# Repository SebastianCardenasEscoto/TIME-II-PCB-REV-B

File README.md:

# TIME-II-PCB-REV-C
Radical Redesign of PCB for TIME II project of Space Technologies at Cal

## Features
- :computer: STM32 Microcontroller
- :hotsprings: Three FFC Plugs for Plate Heating System (Thermistors and Heaters)
- :gear: Two DRV8837 H-Bridge Motor Controllers
- :electric_plug: OR Gate PMIC for switching between USB and Battery Power
- :floppy_disk: SD Card for Data Logging

## Differences between Previous Revision

1. We received notice that we _may_ be able to use batteries outside of Blue Origin's approved battery list. 

Thus we decided to use lithium batteries which allowed the following simplifications:

- &nbsp;&nbsp;&nbsp;&nbsp; No longer support charging on flight
- Replaced buck converter with LDO as voltage drop is now 3.7V -> 3.3V instead of 5V -> 3.3V

2. The following simplifications were allowed due to mechanical design:
- Only support Brushed DC motors instead of supporting both DC motors and 3 pin servos
- Heater ports have been reduced from 5 to 3

3. The ESP32 microcontoller was replaced with an STM32, mostly to reduce board space since the WiFi and Bluetooth antennae that the ESP offers were unnecessary.

## Pictures

### Schematic

### Layout

## To-Do
- SD card footprint - Week of 3/10/24 [DONE]
- MOSI is connected to DAT0, MISO is connected to CMD. It should be: MOSI is connected to CMD, MISO is connected to DAT0.
- Sanity checks for wiring - week of 3/10/24
- Send board for manufacture - week of 3/10/24

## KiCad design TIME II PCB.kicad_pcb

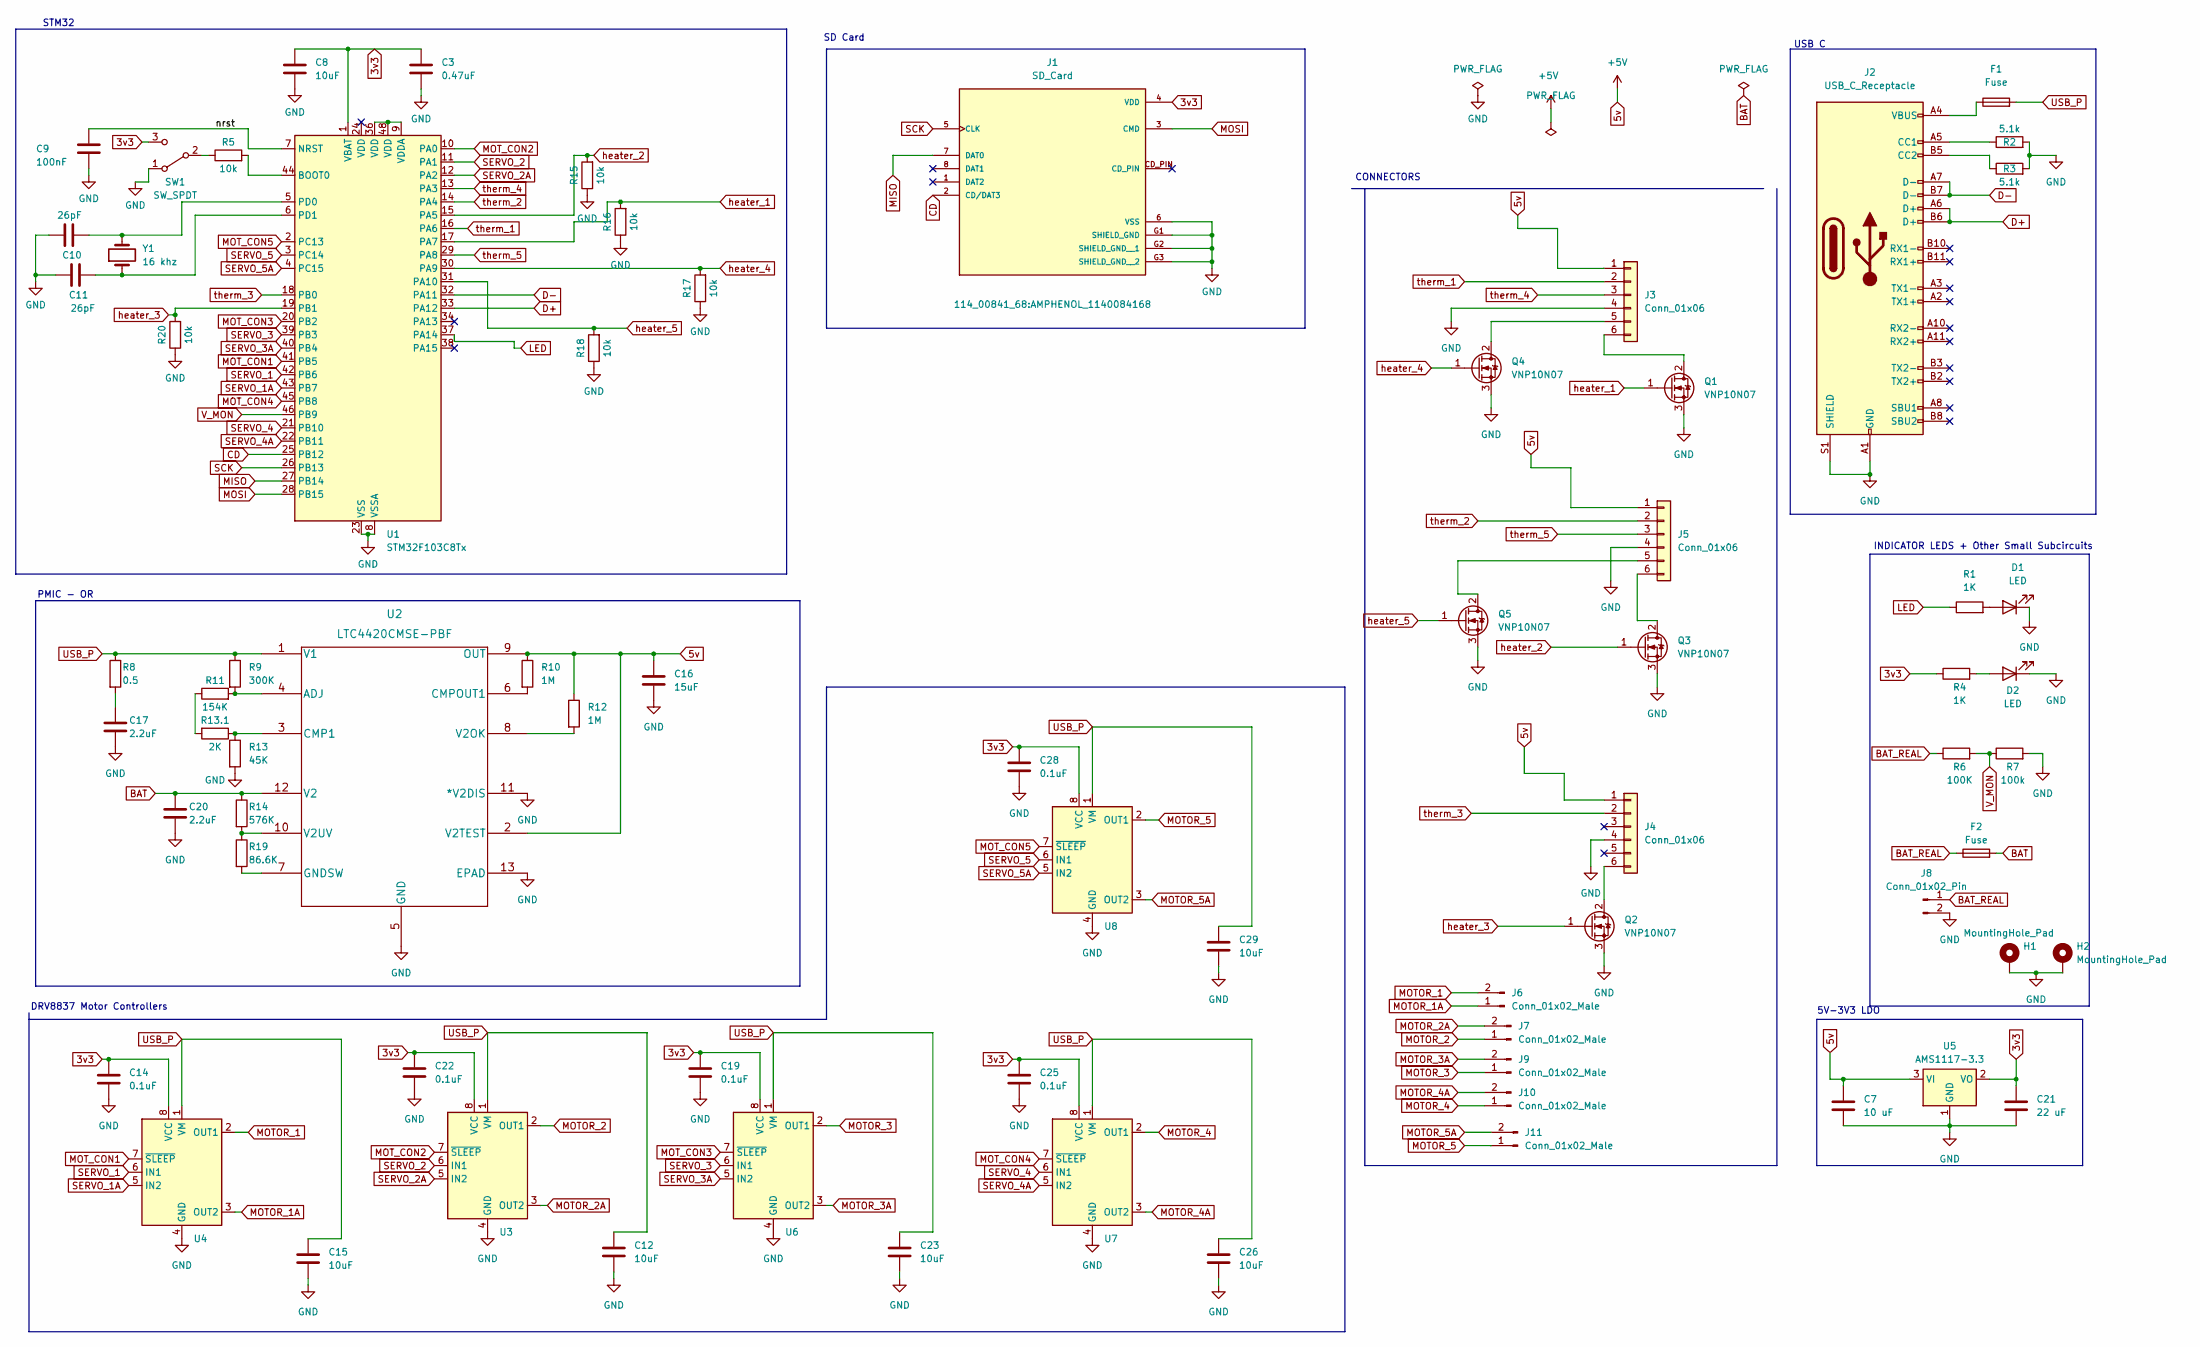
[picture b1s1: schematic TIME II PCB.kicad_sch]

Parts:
C3: 0.47uF; C_0402_1005Metric
C7: 10 uF; C_0402_1005Metric
C8, C12, C15, C23, C26, C29: 10uF; C_0402_1005Metric
C9: 100nF; C_0402_1005Metric
C10, C11: 26pF; C_0402_1005Metric
C14, C19, C22, C25, C28: 0.1uF; C_0402_1005Metric
C16: 15uF; C_0402_1005Metric
C17, C20: 2.2uF; C_0402_1005Metric
C21: 22 uF; C_0402_1005Metric
D1, D2: LED; LED_0603_1608Metric
F1, F2: Fuse; Fuse_0603_1608Metric
H1, H2: MountingHole_Pad; MountingHole_2.5mm_Pad
J1: SD_Card; AMPHENOL_1140084168; PARTREV F
J2: USB_C_Receptacle; USB4105-GF-A
J3, J4, J5: Conn_01x06; CON_525590652_MOL
J6, J7, J9, J10, J11: Conn_01x02_Male; JST_XH_B2B-XH-A_1x02_P2.50mm_Vertical
J8: Conn_01x02_Pin; JST_XH_B2B-XH-AM_1x02_P2.50mm_Vertical
Q1, Q2, Q3, Q4, Q5: VNP10N07; SOT-23-3
R1, R4: 1K; R_0402_1005Metric
R2, R3: 5.1k; R_0402_1005Metric
R5, R15, R16, R17, R18, R20: 10k; R_0402_1005Metric
R6: 100K; R_0402_1005Metric
R7: 100k; R_0402_1005Metric
R8: 0.5; R_0402_1005Metric
R9: 300K; R_0603_1608Metric
R10, R12: 1M; R_0402_1005Metric
R11: 2K; R_0603_1608Metric
R13: 45K; R_0603_1608Metric
R13.1: 154K; R_0603_1608Metric
R14: 576K; R_0402_1005Metric
R19: 86.6K; R_0402_1005Metric
SW1: SW_SPDT; PinHeader_1x03_P1.27mm_Vertical
U1: STM32F103C8Tx; LQFP-48_7x7mm_P0.5mm
U2: LTC4420CMSE-PBF; MSOP-12-1EP_3x4mm_P0.65mm_EP1.65x2.85mm
U3, U4, U6, U7, U8: WSON-8-1EP_2x2mm_P0.5mm_EP0.9x1.6mm_ThermalVias
U5: AMS1117-3.3; SOT-223-3_TabPin2
Y1: 16 khz; abm3

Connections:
3v3: C3.1, C8.1, C14.1, C19.1, C21.1, C22.1, C25.1, C28.1, J1.4 (VDD), R4.1, SW1.3 (C), U1.1 (VBAT), U3.8 (VCC), U4.8 (VCC), U5.2 (VO), U6.8 (VCC), U7.8 (VCC), U8.8 (VCC)
5v: C7.1, C16.1, J3.1, J4.1, J5.1, R10.1, R12.1, U2.2 (V2TEST), U2.9 (OUT), U5.3 (VI)
/nrst: C9.1, U1.7 (NRST)
BAT: C20.1, F2.2, R14.1, U2.12 (V2)
BAT_REAL: F2.1, J8.1, R6.1
CD: J1.2 (CD/DAT3), U1.25 (PB12)
D+: J2.A6 (D+), J2.B6 (D+), U1.33 (PA12)
D-: J2.A7 (D-), J2.B7 (D-), U1.32 (PA11)
GND: C3.2, C7.2, C8.2, C9.2, C10.1, C11.1, C12.2, C14.2, C15.2, C16.2, C17.2, C19.2, C20.2, C21.2, C22.2, C23.2, C25.2, C26.2, C28.2, C29.2, D1.1 (K), D2.1 (K), H1.1, H2.1, J1.6 (VSS), J1.G1 (SHIELD_GND), J1.G2 (SHIELD_GND__1), J1.G3 (SHIELD_GND__2), J2.A1 (GND), J2.A12 (GND), J2.B1 (GND), J2.B12 (GND), J2.S1 (SHIELD), J3.4, J4.4, J5.4, J8.2, Q1.3 (S), Q2.3 (S), Q3.3 (S), Q4.3 (S), Q5.3 (S), R2.2, R3.2, R7.2, R13.2, R15.1, R16.1, R17.1, R18.1, R20.1, SW1.1 (A), U1.8 (VSSA), U1.23 (VSS), U1.35 (VSS), U1.47 (VSS), U2.5 (GND), U2.11 (*V2DIS), U2.13 (EPAD), U3.4 (GND), U3.9 (GND), U4.4 (GND), U4.9 (GND), U5.1 (GND), U6.4 (GND), U6.9 (GND), U7.4 (GND), U7.9 (GND), U8.4 (GND), U8.9 (GND)
LED: R1.1, U1.37 (PA14)
MISO: J1.7 (DAT0), U1.27 (PB14)
MOSI: J1.3 (CMD), U1.28 (PB15)
MOTOR_1: J6.2, U4.2 (OUT1)
MOTOR_1A: J6.1, U4.3 (OUT2)
MOTOR_2: J7.1, U3.2 (OUT1)
MOTOR_2A: J7.2, U3.3 (OUT2)
MOTOR_3: J9.1, U6.2 (OUT1)
MOTOR_3A: J9.2, U6.3 (OUT2)
MOTOR_4: J10.1, U7.2 (OUT1)
MOTOR_4A: J10.2, U7.3 (OUT2)
MOTOR_5: J11.1, U8.2 (OUT1)
MOTOR_5A: J11.2, U8.3 (OUT2)
MOT_CON1: U1.41 (PB5), U4.7 (~SLEEP)
MOT_CON2: U1.10 (PA0), U3.7 (~SLEEP)
MOT_CON3: U1.20 (PB2), U6.7 (~SLEEP)
MOT_CON4: U1.45 (PB8), U7.7 (~SLEEP)
MOT_CON5: U1.2 (PC13), U8.7 (~SLEEP)
unnamed: C17.1, R8.2
unnamed: D1.2 (A), R1.2
unnamed: D2.2 (A), R4.2
unnamed: F1.1, J2.A4 (VBUS), J2.A9 (VBUS), J2.B4 (VBUS), J2.B9 (VBUS)
unnamed: J2.A5 (CC1), R2.1
unnamed: J2.B5 (CC2), R3.1
unnamed: J3.5, Q4.2 (D)
unnamed: J3.6, Q1.2 (D)
unnamed: J4.6, Q2.2 (D)
unnamed: J5.5, Q5.2 (D)
unnamed: J5.6, Q3.2 (D)
unnamed: R11.1, R13.1.2
unnamed: R5.1, SW1.2 (B)
unnamed: R5.2, U1.44 (BOOT0)
unnamed: C10.2, U1.5 (PD0), Y1.2
unnamed: C11.2, U1.6 (PD1), Y1.1
unnamed: U1.9 (VDDA), U1.36 (VDD), U1.48 (VDD)
unnamed: R9.2, R11.2, U2.4 (ADJ)
unnamed: R13.1, R13.1.1, U2.3 (CMP1)
unnamed: R10.2, U2.6 (CMPOUT1)
unnamed: R19.2, U2.7 (GNDSW)
unnamed: R12.2, U2.8 (V2OK)
unnamed: R14.2, R19.1, U2.10 (V2UV)
SCK: J1.5 (CLK), U1.26 (PB13)
SERVO_1: U1.42 (PB6), U4.6 (IN1)
SERVO_1A: U1.43 (PB7), U4.5 (IN2)
SERVO_2: U1.11 (PA1), U3.6 (IN1)
SERVO_2A: U1.12 (PA2), U3.5 (IN2)
SERVO_3: U1.39 (PB3), U6.6 (IN1)
SERVO_3A: U1.40 (PB4), U6.5 (IN2)
SERVO_4: U1.21 (PB10), U7.6 (IN1)
SERVO_4A: U1.22 (PB11), U7.5 (IN2)
SERVO_5: U1.3 (PC14), U8.6 (IN1)
SERVO_5A: U1.4 (PC15), U8.5 (IN2)
USB_P: C12.1, C15.1, C23.1, C26.1, C29.1, F1.2, R8.1, R9.1, U2.1 (V1), U3.1 (VM), U4.1 (VM), U6.1 (VM), U7.1 (VM), U8.1 (VM)
V_MON: R6.2, R7.1, U1.46 (PB9)
heater_1: Q1.1 (G), R16.2, U1.17 (PA7)
heater_2: Q3.1 (G), R15.2, U1.15 (PA5)
heater_3: Q2.1 (G), R20.2, U1.19 (PB1)
heater_4: Q4.1 (G), R17.2, U1.30 (PA9)
heater_5: Q5.1 (G), R18.2, U1.31 (PA10)
therm_1: J3.2, U1.16 (PA6)
therm_2: J5.2, U1.14 (PA4)
therm_3: J4.2, U1.18 (PB0)
therm_4: J3.3, U1.13 (PA3)
therm_5: J5.3, U1.29 (PA8)

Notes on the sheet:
DRV8837 Motor Controllers
INDICATOR LEDS + Other Small Subcircuits
STM32
SD Card
PMIC - OR
USB C
5V-3V3 LDO
CONNECTORS

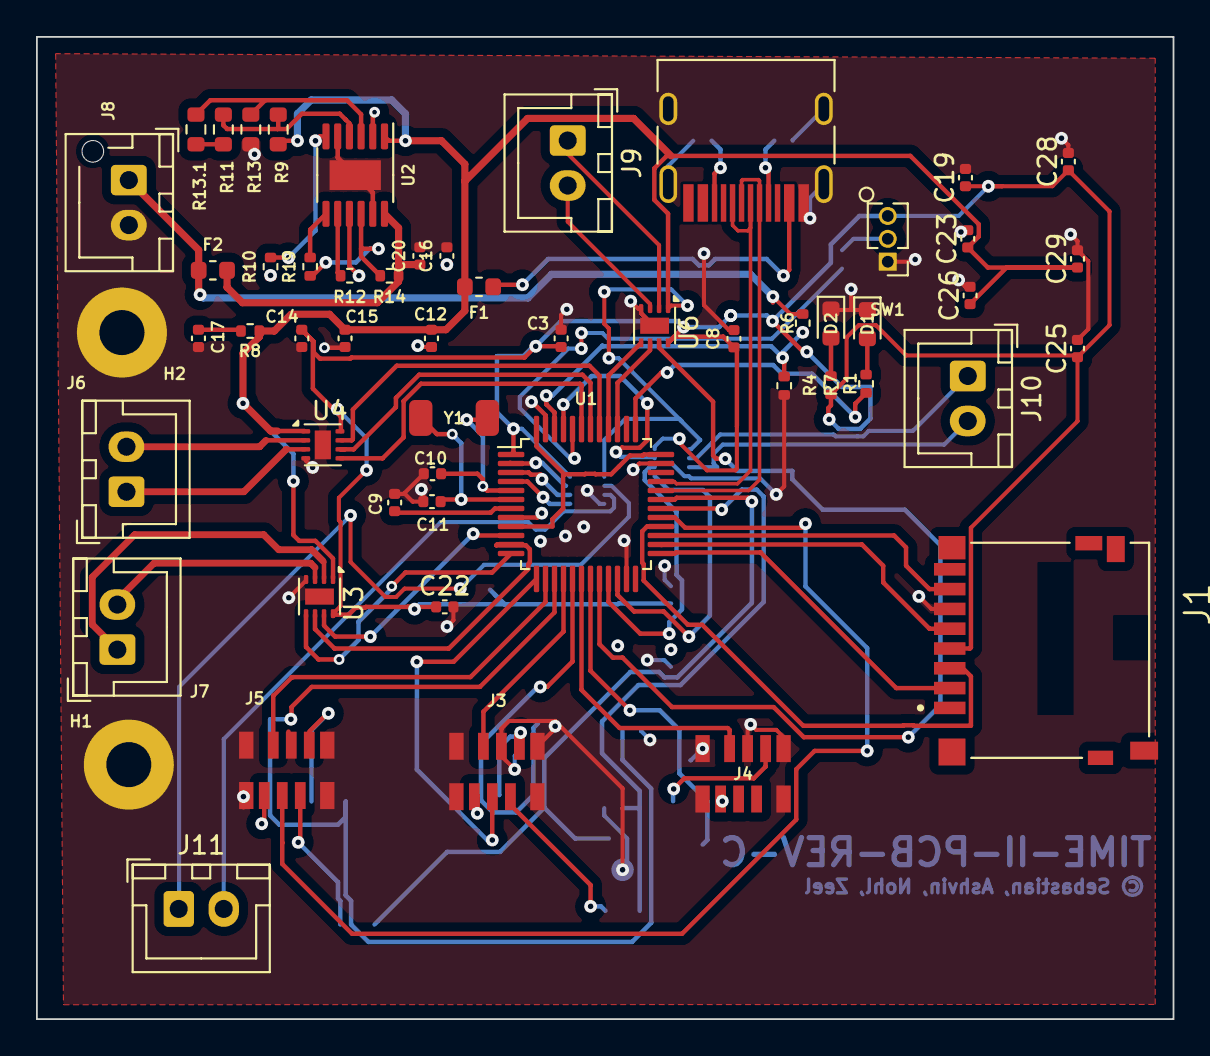
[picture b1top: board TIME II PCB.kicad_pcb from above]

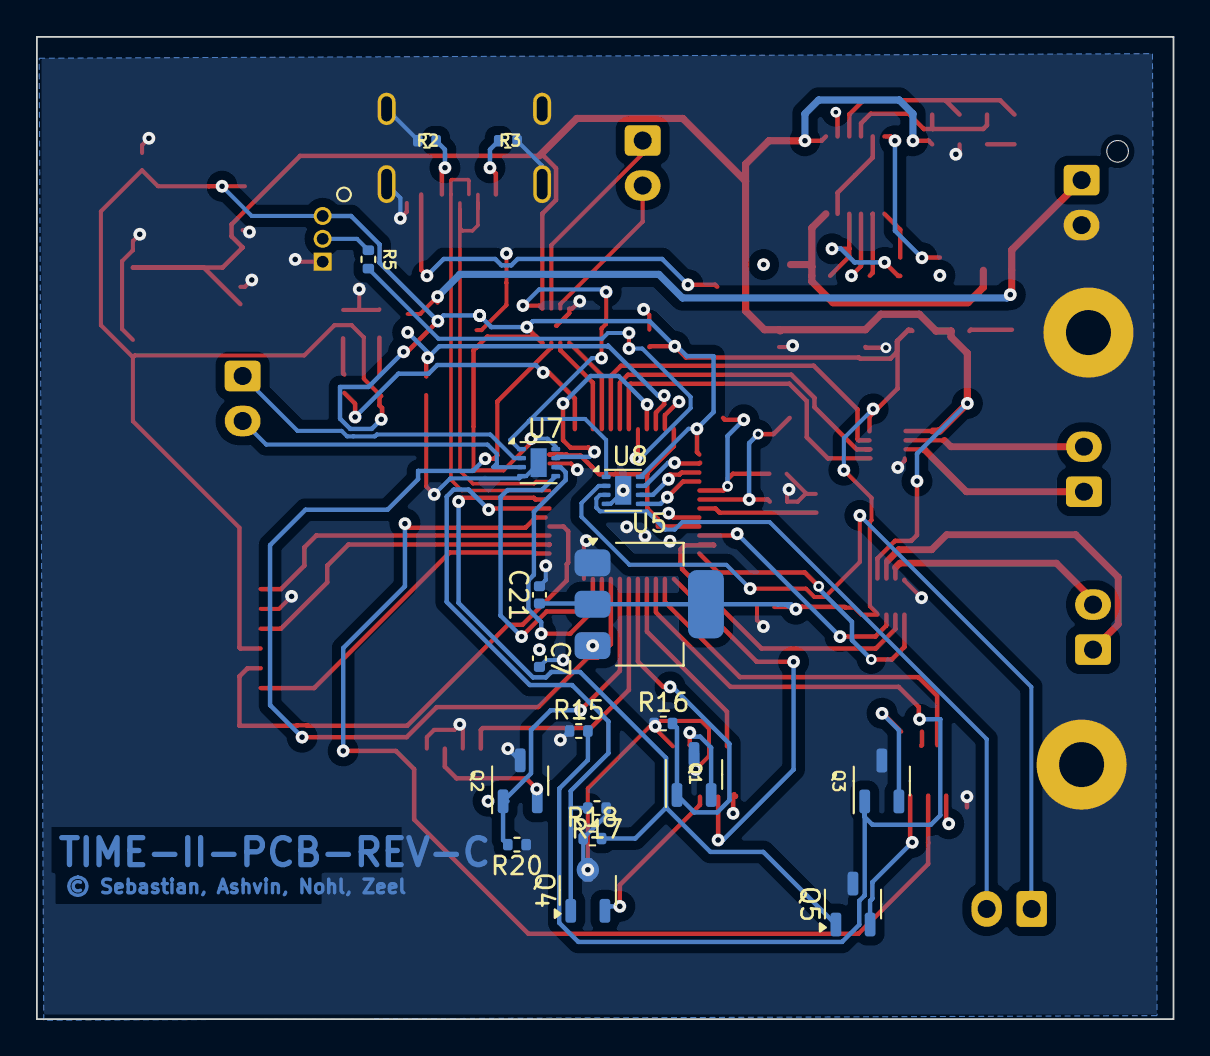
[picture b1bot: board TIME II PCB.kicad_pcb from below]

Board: 4 copper layers, 63.1 x 54.6 mm, 73 parts (18 on the bottom side), 73 nets.

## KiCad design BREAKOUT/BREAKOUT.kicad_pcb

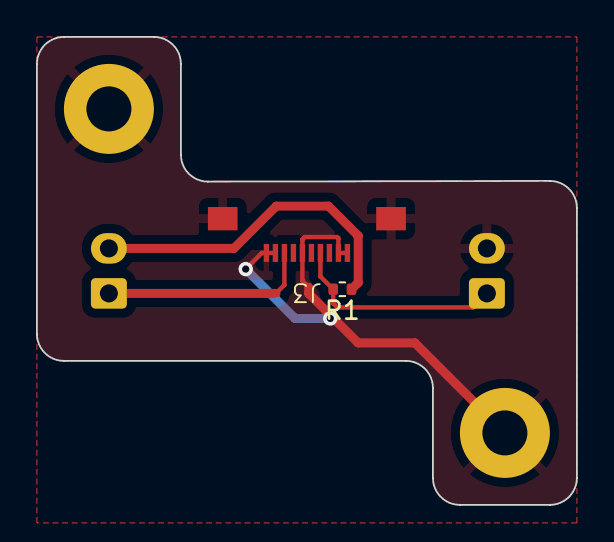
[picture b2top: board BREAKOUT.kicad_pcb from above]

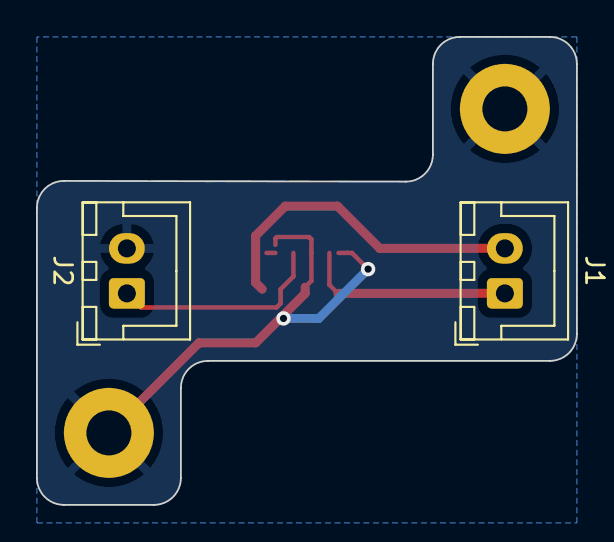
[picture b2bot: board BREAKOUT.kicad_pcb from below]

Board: 2 copper layers, 30.0 x 26.0 mm, 6 parts (2 on the bottom side), 4 nets.

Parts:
H1, H2: MountingHole_Pad; MountingHole_2.5mm_Pad
J1, J2: Conn_01x02_Male; JST_XH_B2B-XH-A_1x02_P2.50mm_Vertical
J3: Conn_01x06; horizontal
R1: 100k; R_0402_1005Metric

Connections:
5v: J1.2, J3.1, R1.1
GND: H1.1, H2.1, J2.2, J3.4
heater_3: J1.1, J3.6
therm_3: J2.1, J3.2, R1.2

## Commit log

2023-04-25 Project Parts
2023-09-14 layout
2023-09-21 motor driver
2023-09-25 done?
2023-11-05 new board
2024-02-24 main (old rev) local changes push
2024-04-01 new board layout
2024-04-04 trying to push this pcb up into the clouds
2024-07-21 major reroute
2024-07-21 ldo added back
2024-09-26 thicker power rails
2024-09-26 README
2024-10-01 week of 01/10/24
2024-10-07 sd card update
2024-10-10 Updated schem
2024-11-22 latest revision

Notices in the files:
TIME II PCB.kicad_pcb:
© Sebastian, Ashvin, Nohl, Zeel
parts and their libraries:
Copyright 2021 Accelerated Designs. All rights reserved.
